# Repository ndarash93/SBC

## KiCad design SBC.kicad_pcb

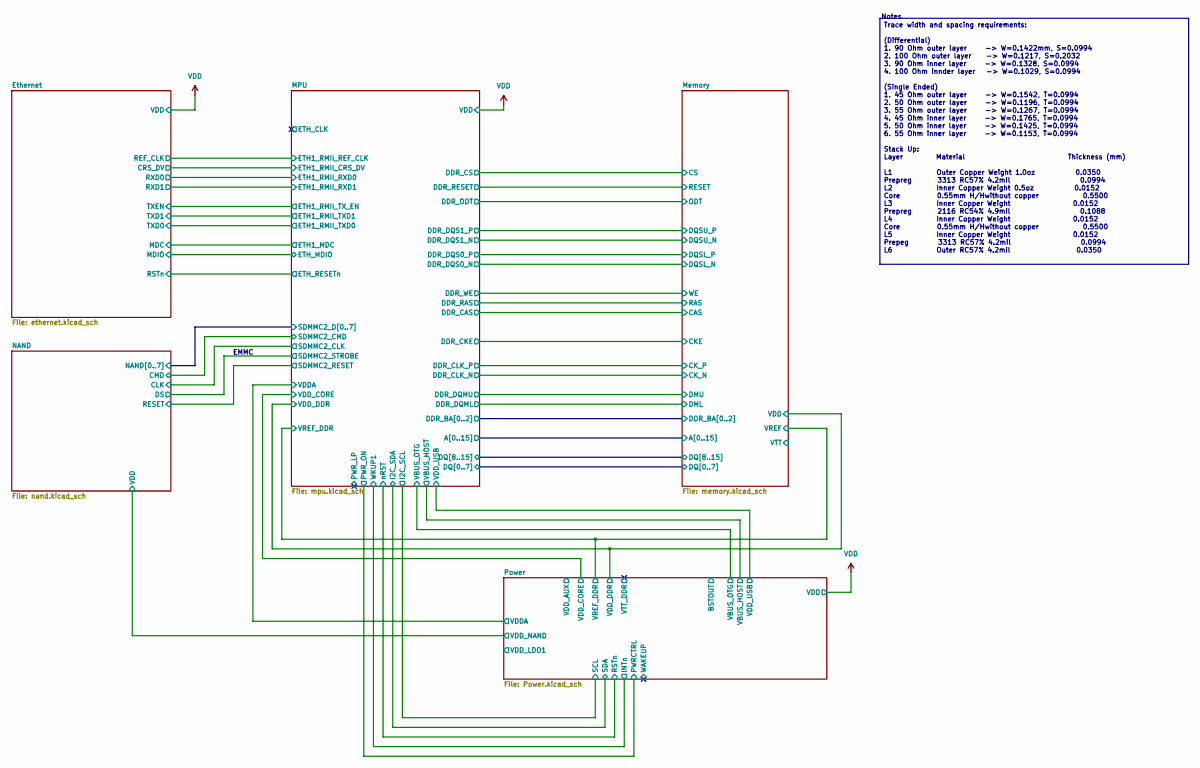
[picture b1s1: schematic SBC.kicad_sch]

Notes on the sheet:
Notes
EMMC
Trace width and spacing requirements: (Differential) 1. 90 Ohm outer layer -> W=0.1422mm, S=0.0994 2. 100 Ohm outer layer -> W=0.1217, S=0.2032 3. 90 Ohm inner layer -> W=0.1328, S=0.0994 4. 100 Ohm innder layer -> W=0.1029, S=0.0994 (Single Ended) 1. 45 Ohm outer layer -> W=0.1542, T=0.0994 2. 50 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

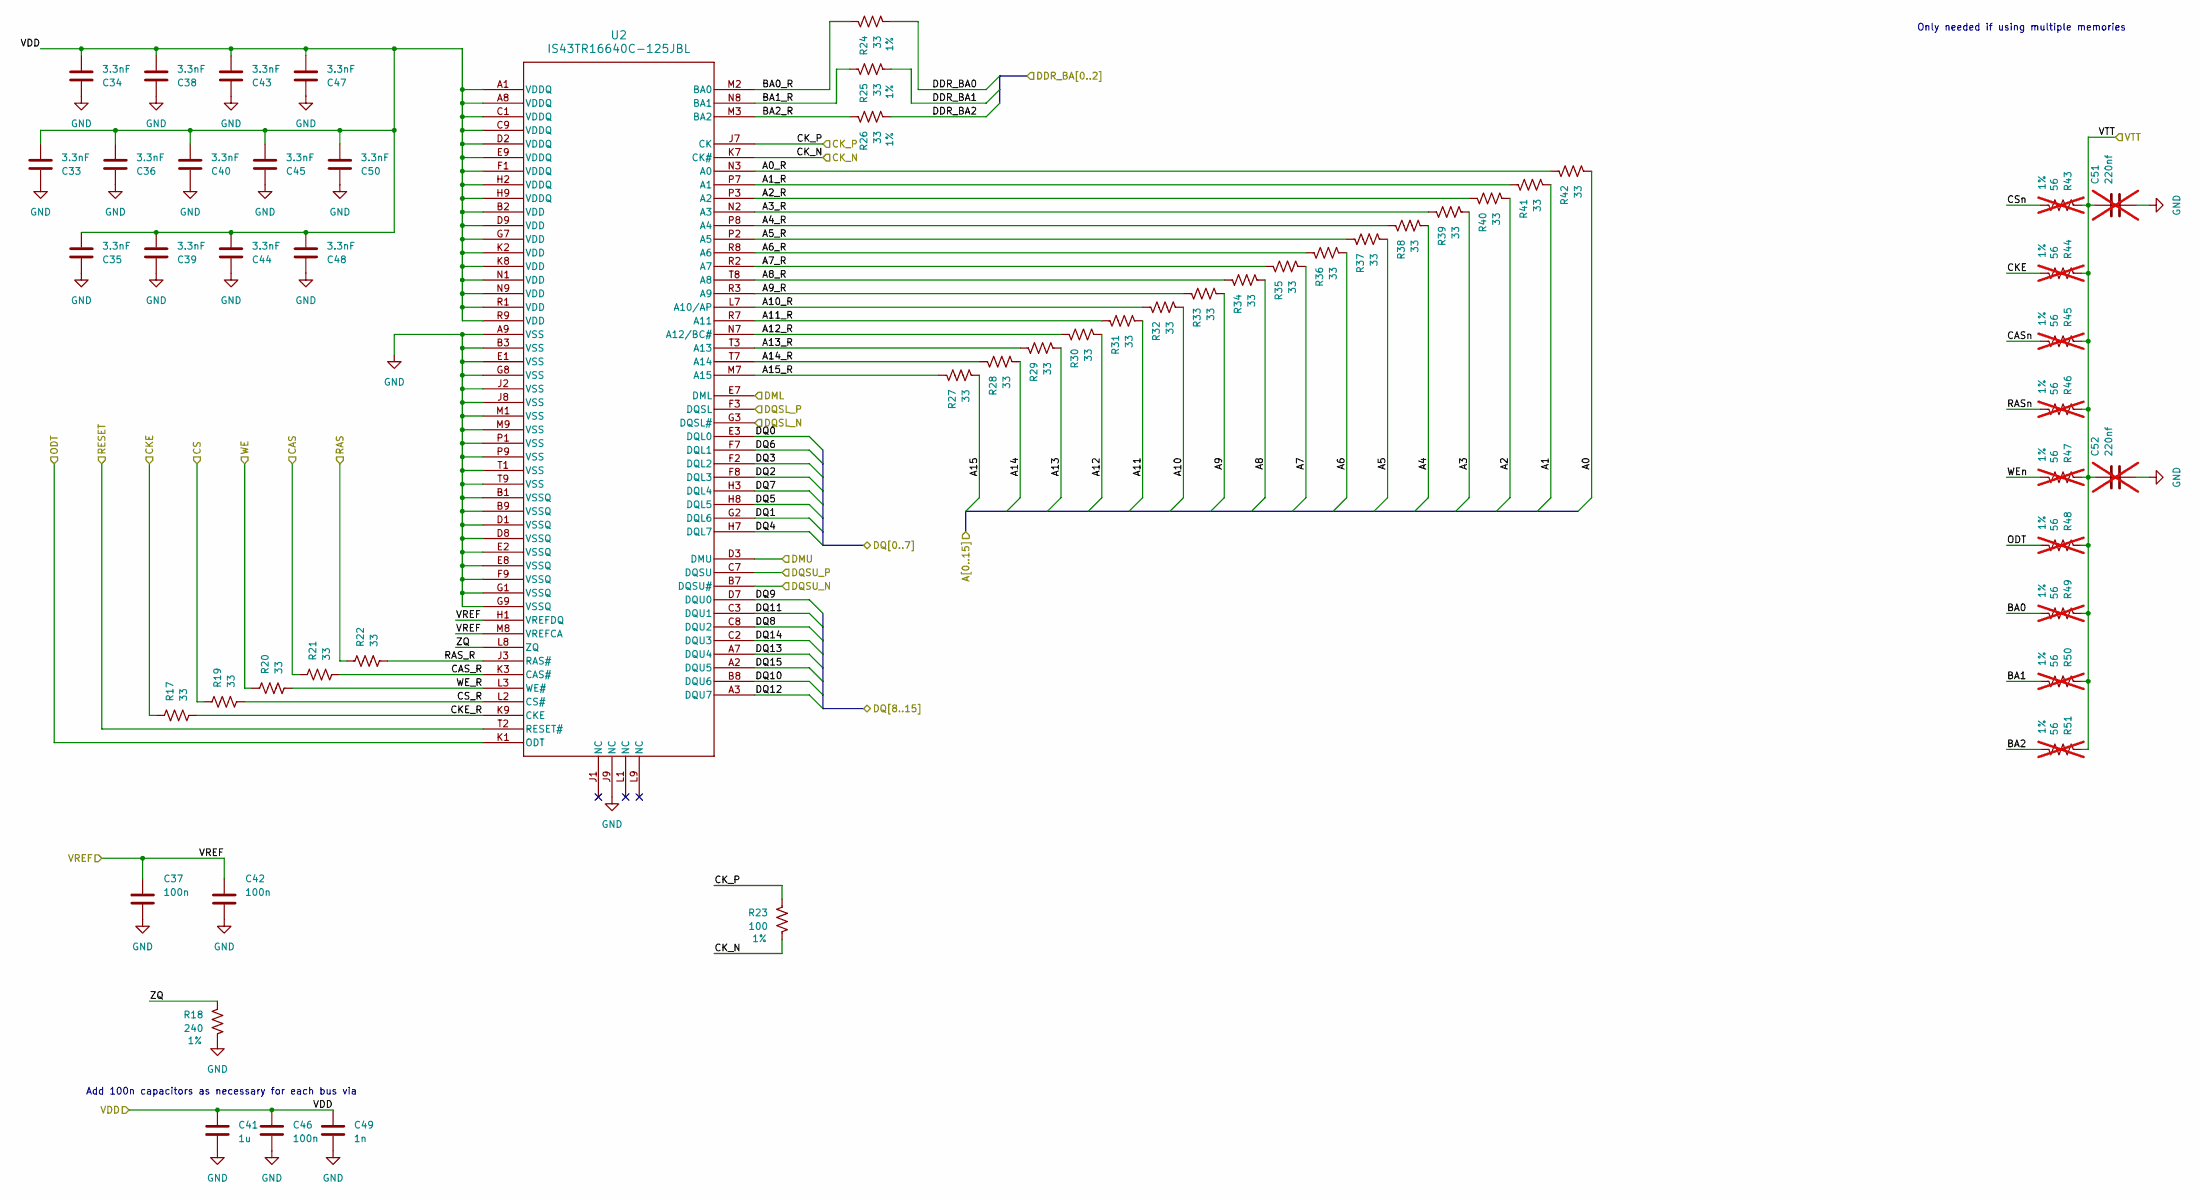
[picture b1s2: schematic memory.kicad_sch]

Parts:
C33, C34, C35, C36, C38, C39, C40, C43, C44, C45, C47, C48, C50: 3.3nF; C_0201_0603Metric
C37, C42: 100n; C_0201_0603Metric
C41: 1u; C_0402_1005Metric
C46: 100n; C_0402_1005Metric
C49: 1n; C_0201_0603Metric
C51, C52: 220nf; TBD; not fitted
R17, R19, R20, R21, R22, R24, R25, R26, R27, R28, R29, R30, R31, R32, R33, R34, R35, R36, R37, R38, R39, R40, R41, R42: 33; R_0402_1005Metric
R18: 240; R_0201_0603Metric
R23: 100; R_0201_0603Metric
R43, R44, R45, R46, R47, R48, R49, R50, R51: 56; not fitted
U2: IS43TR16640C-125JBL; TW-BGA96L_9X13X1.2_ISI

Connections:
/MPU/A0: R42.2; also elsewhere on the board
/MPU/A1: R41.2; also elsewhere on the board
/MPU/A2: R40.2; also elsewhere on the board
/MPU/A3: R39.2; also elsewhere on the board
/MPU/A4: R38.2; also elsewhere on the board
/MPU/A5: R37.2; also elsewhere on the board
/MPU/A6: R36.2; also elsewhere on the board
/MPU/A7: R35.2; also elsewhere on the board
/MPU/A8: R34.2; also elsewhere on the board
/MPU/A9: R33.2; also elsewhere on the board
/MPU/A10: R32.2; also elsewhere on the board
/MPU/A11: R31.2; also elsewhere on the board
/MPU/A12: R30.2; also elsewhere on the board
/MPU/A13: R29.2; also elsewhere on the board
/MPU/A14: R28.2; also elsewhere on the board
/MPU/A15: R27.2; also elsewhere on the board
/MPU/DDR_BA0: R24.2; also elsewhere on the board
/MPU/DDR_BA1: R25.2; also elsewhere on the board
/MPU/DDR_BA2: R26.2; also elsewhere on the board
/MPU/DDR_CAS: R21.1; also elsewhere on the board
/MPU/DDR_CKE: R17.1; also elsewhere on the board
/MPU/DDR_CLKN: R23.2, U2.K7 (CK#); also elsewhere on the board
/MPU/DDR_CLKP: R23.1, U2.J7 (CK); also elsewhere on the board
/MPU/DDR_CS: R19.1; also elsewhere on the board
/MPU/DDR_DQM0: U2.E7 (DML); also elsewhere on the board
/MPU/DDR_DQM1: U2.D3 (DMU); also elsewhere on the board
/MPU/DDR_DQS0_N: U2.G3 (DQSL#); also elsewhere on the board
/MPU/DDR_DQS0_P: U2.F3 (DQSL); also elsewhere on the board
/MPU/DDR_DQS1_N: U2.B7 (DQSU#); also elsewhere on the board
/MPU/DDR_DQS1_P: U2.C7 (DQSU); also elsewhere on the board
/MPU/DDR_RAS: R22.1; also elsewhere on the board
/MPU/DDR_RESETn: U2.T2 (RESET#); also elsewhere on the board
/MPU/DDR_VREF: C37.1, C42.1, U2.H1 (VREFDQ), U2.M8 (VREFCA); also elsewhere on the board
/MPU/DDR_WE: R20.1; also elsewhere on the board
/MPU/DQ0: U2.E3 (DQL0); also elsewhere on the board
/MPU/DQ1: U2.G2 (DQL6); also elsewhere on the board
/MPU/DQ2: U2.F8 (DQL3); also elsewhere on the board
/MPU/DQ3: U2.F2 (DQL2); also elsewhere on the board
/MPU/DQ4: U2.H7 (DQL7); also elsewhere on the board
/MPU/DQ5: U2.H8 (DQL5); also elsewhere on the board
/MPU/DQ6: U2.F7 (DQL1); also elsewhere on the board
/MPU/DQ7: U2.H3 (DQL4); also elsewhere on the board
/MPU/DQ8: U2.C8 (DQU2); also elsewhere on the board
/MPU/DQ9: U2.D7 (DQU0); also elsewhere on the board
/MPU/DQ10: U2.B8 (DQU6); also elsewhere on the board
/MPU/DQ11: U2.C3 (DQU1); also elsewhere on the board
/MPU/DQ12: U2.A3 (DQU7); also elsewhere on the board
/MPU/DQ13: U2.A7 (DQU4); also elsewhere on the board
/MPU/DQ14: U2.C2 (DQU3); also elsewhere on the board
/MPU/DQ15: U2.A2 (DQU5); also elsewhere on the board
/MPU/VDD_DDR: C33.1, C34.1, C35.1, C36.1, C38.1, C39.1, C40.1, C41.1, C43.1, C44.1, C45.1, C46.1, C47.1, C48.1, C49.1, C50.1, U2.A1 (VDDQ), U2.A8 (VDDQ), U2.B2 (VDD), U2.C1 (VDDQ), U2.C9 (VDDQ), U2.D2 (VDDQ), U2.D9 (VDD), U2.E9 (VDDQ), U2.F1 (VDDQ), U2.G7 (VDD), U2.H2 (VDDQ), U2.H9 (VDDQ), U2.K2 (VDD), U2.K8 (VDD), U2.N1 (VDD), U2.N9 (VDD), U2.R1 (VDD), U2.R9 (VDD); also elsewhere on the board
/Memory/A0_R: R42.1, U2.N3 (A0)
/Memory/A1_R: R41.1, U2.P7 (A1)
/Memory/A2_R: R40.1, U2.P3 (A2)
/Memory/A3_R: R39.1, U2.N2 (A3)
/Memory/A4_R: R38.1, U2.P8 (A4)
/Memory/A5_R: R37.1, U2.P2 (A5)
/Memory/A6_R: R36.1, U2.R8 (A6)
/Memory/A7_R: R35.1, U2.R2 (A7)
/Memory/A8_R: R34.1, U2.T8 (A8)
/Memory/A9_R: R33.1, U2.R3 (A9)
/Memory/A10_R: R32.1, U2.L7 (A10/AP)
/Memory/A11_R: R31.1, U2.R7 (A11)
/Memory/A12_R: R30.1, U2.N7 (A12/BC#)
/Memory/A13_R: R29.1, U2.T3 (A13)
/Memory/A14_R: R28.1, U2.T7 (A14)
/Memory/A15_R: R27.1, U2.M7 (A15)
/Memory/BA0_R: R24.1, U2.M2 (BA0)
/Memory/BA1_R: R25.1, U2.N8 (BA1)
/Memory/BA2_R: R26.1, U2.M3 (BA2)
/Memory/CAS_R: R21.2, U2.K3 (CAS#)
/Memory/CKE_R: R17.2, U2.K9 (CKE)
/Memory/CS_R: R19.2, U2.L2 (CS#)
/Memory/ODT: U2.K1 (ODT); also elsewhere on the board
/Memory/RAS_R: R22.2, U2.J3 (RAS#)
/Memory/WE_R: R20.2, U2.L3 (WE#)
/Memory/ZQ: R18.1, U2.L8 (ZQ)
GND: C33.2, C34.2, C35.2, C36.2, C37.2, C38.2, C39.2, C40.2, C41.2, C42.2, C43.2, C44.2, C45.2, C46.2, C47.2, C48.2, C49.2, C50.2, C51.2, C52.2, R18.2, U2.A9 (VSS), U2.B1 (VSSQ), U2.B3 (VSS), U2.B9 (VSSQ), U2.D1 (VSSQ), U2.D8 (VSSQ), U2.E1 (VSS), U2.E2 (VSSQ), U2.E8 (VSSQ), U2.F9 (VSSQ), U2.G1 (VSSQ), U2.G8 (VSS), U2.G9 (VSSQ), U2.J2 (VSS), U2.J8 (VSS), U2.J9 (NC), U2.M1 (VSS), U2.M9 (VSS), U2.P1 (VSS), U2.P9 (VSS), U2.T1 (VSS), U2.T9 (VSS); also elsewhere on the board
unnamed: C51.1, C52.1, R43.1, R44.1, R45.1, R46.1, R47.1, R48.1, R49.1, R50.1, R51.1

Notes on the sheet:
Add 100n capacitors as necessary for each bus via
Only needed if using multiple memories

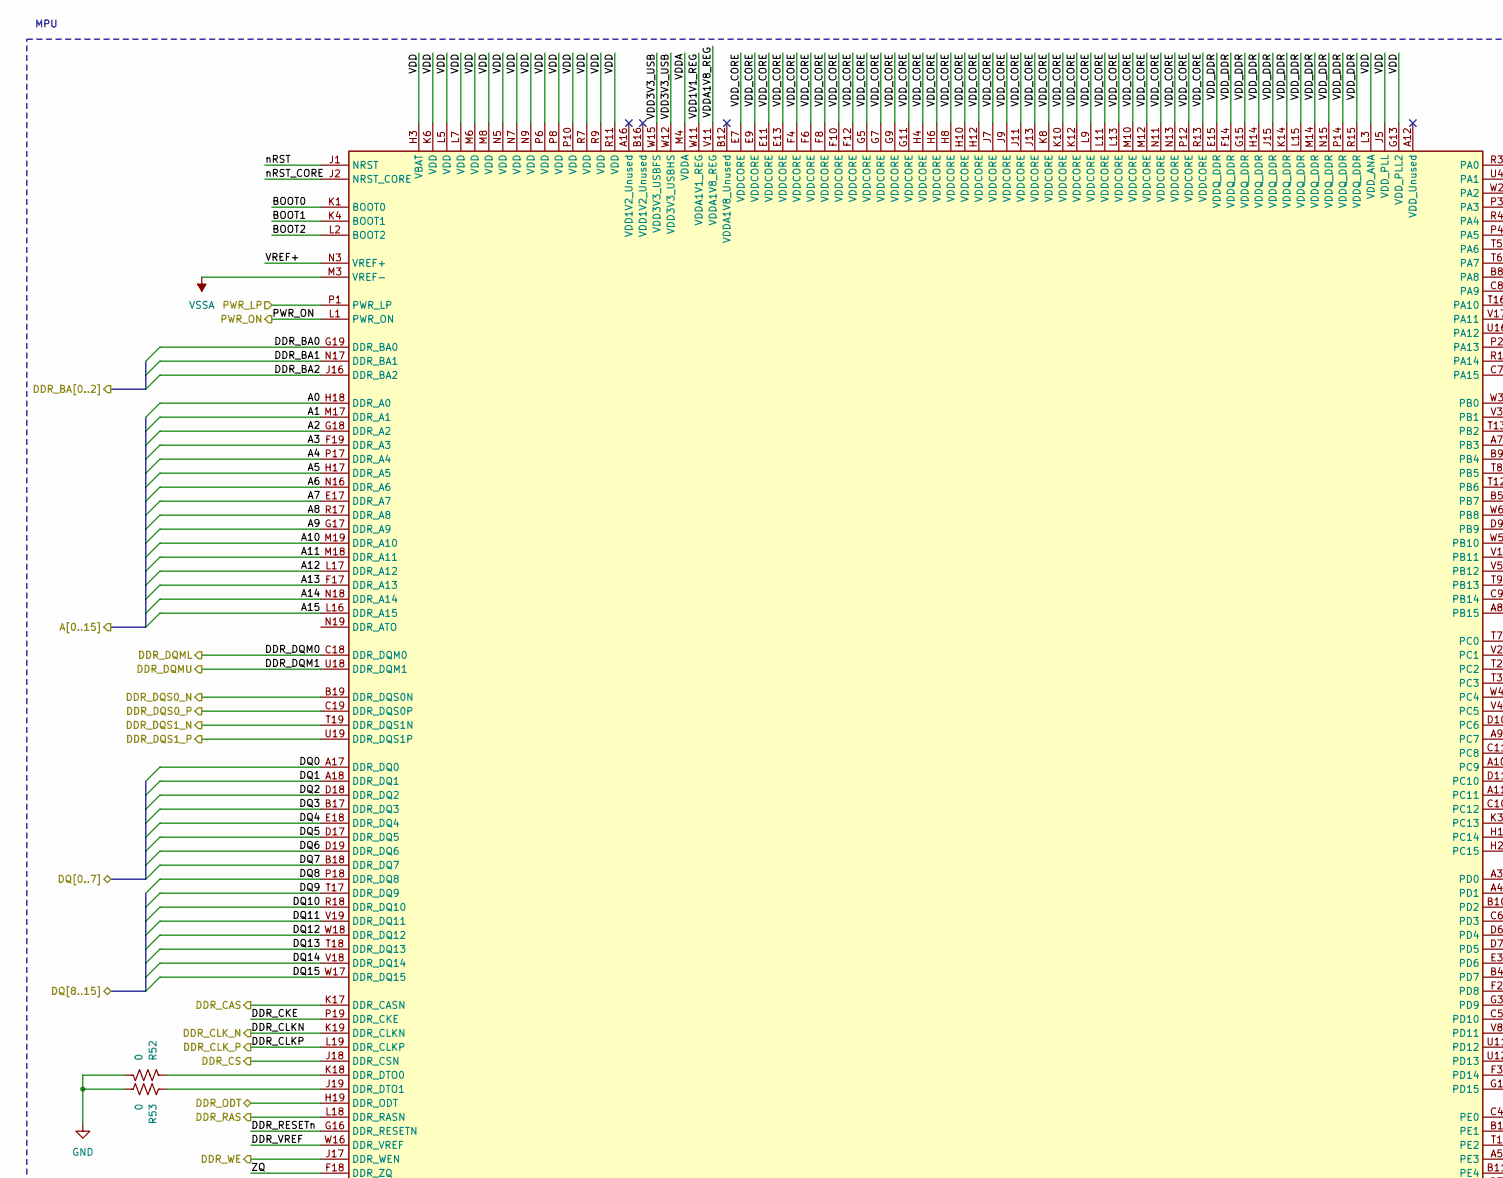
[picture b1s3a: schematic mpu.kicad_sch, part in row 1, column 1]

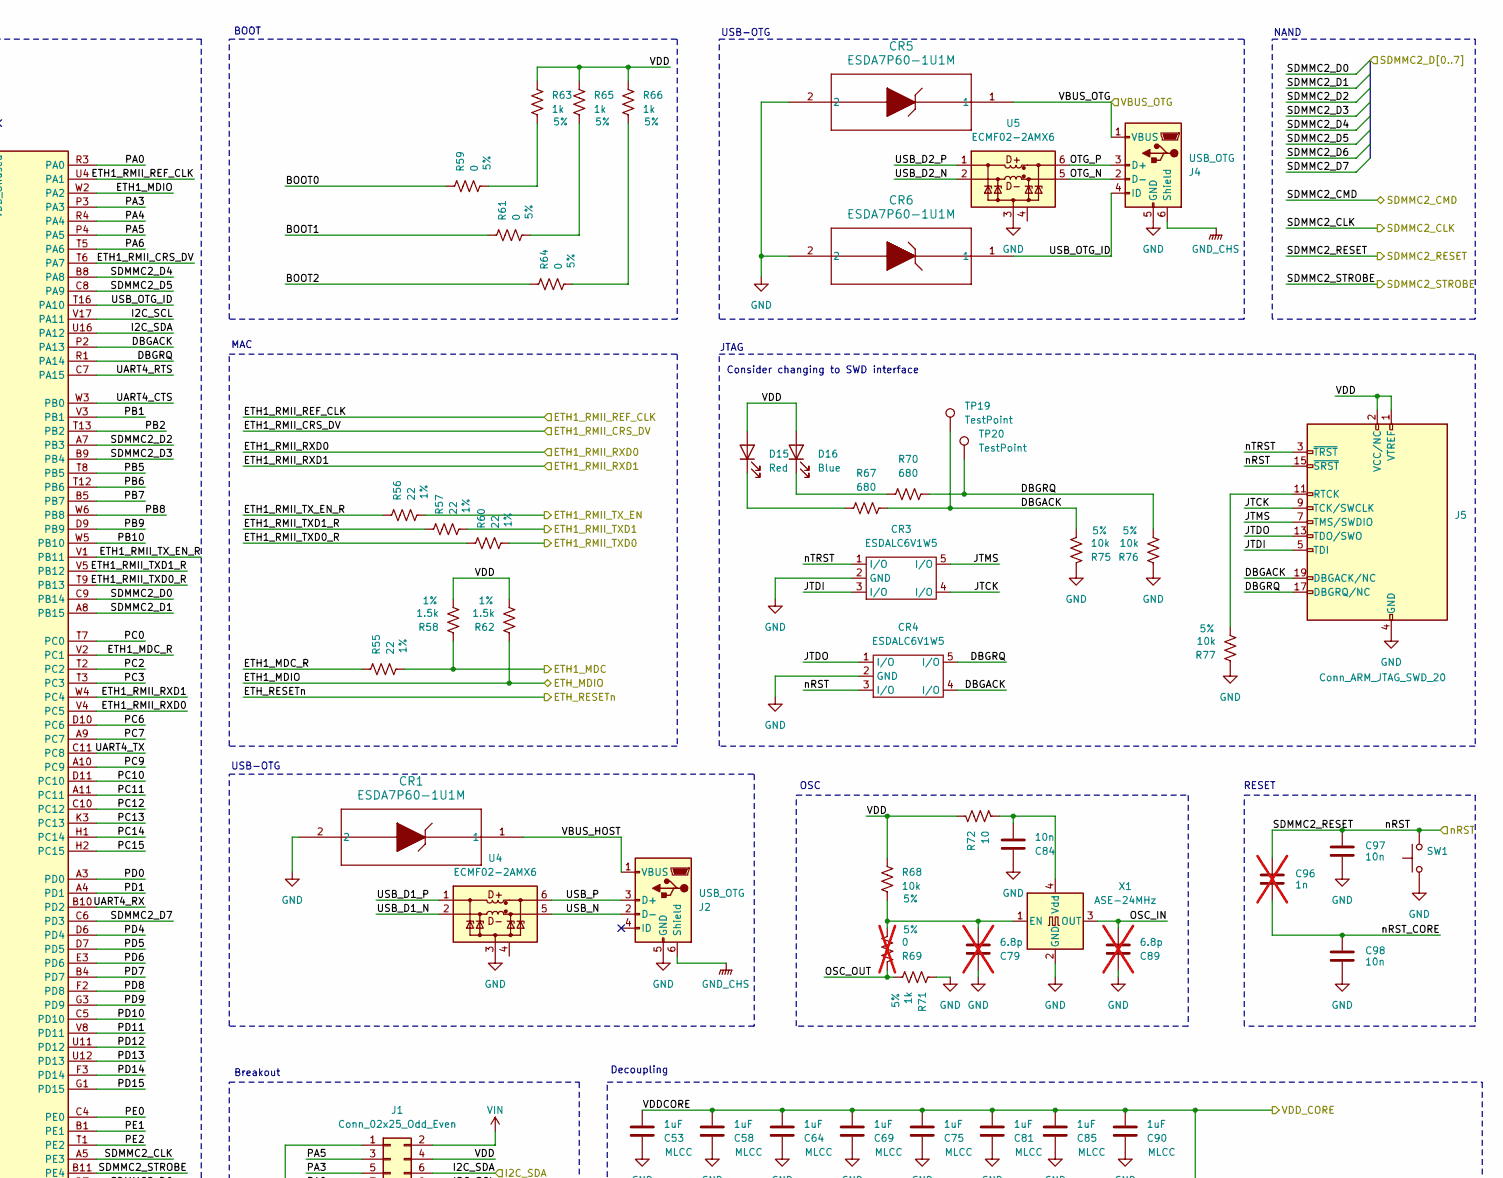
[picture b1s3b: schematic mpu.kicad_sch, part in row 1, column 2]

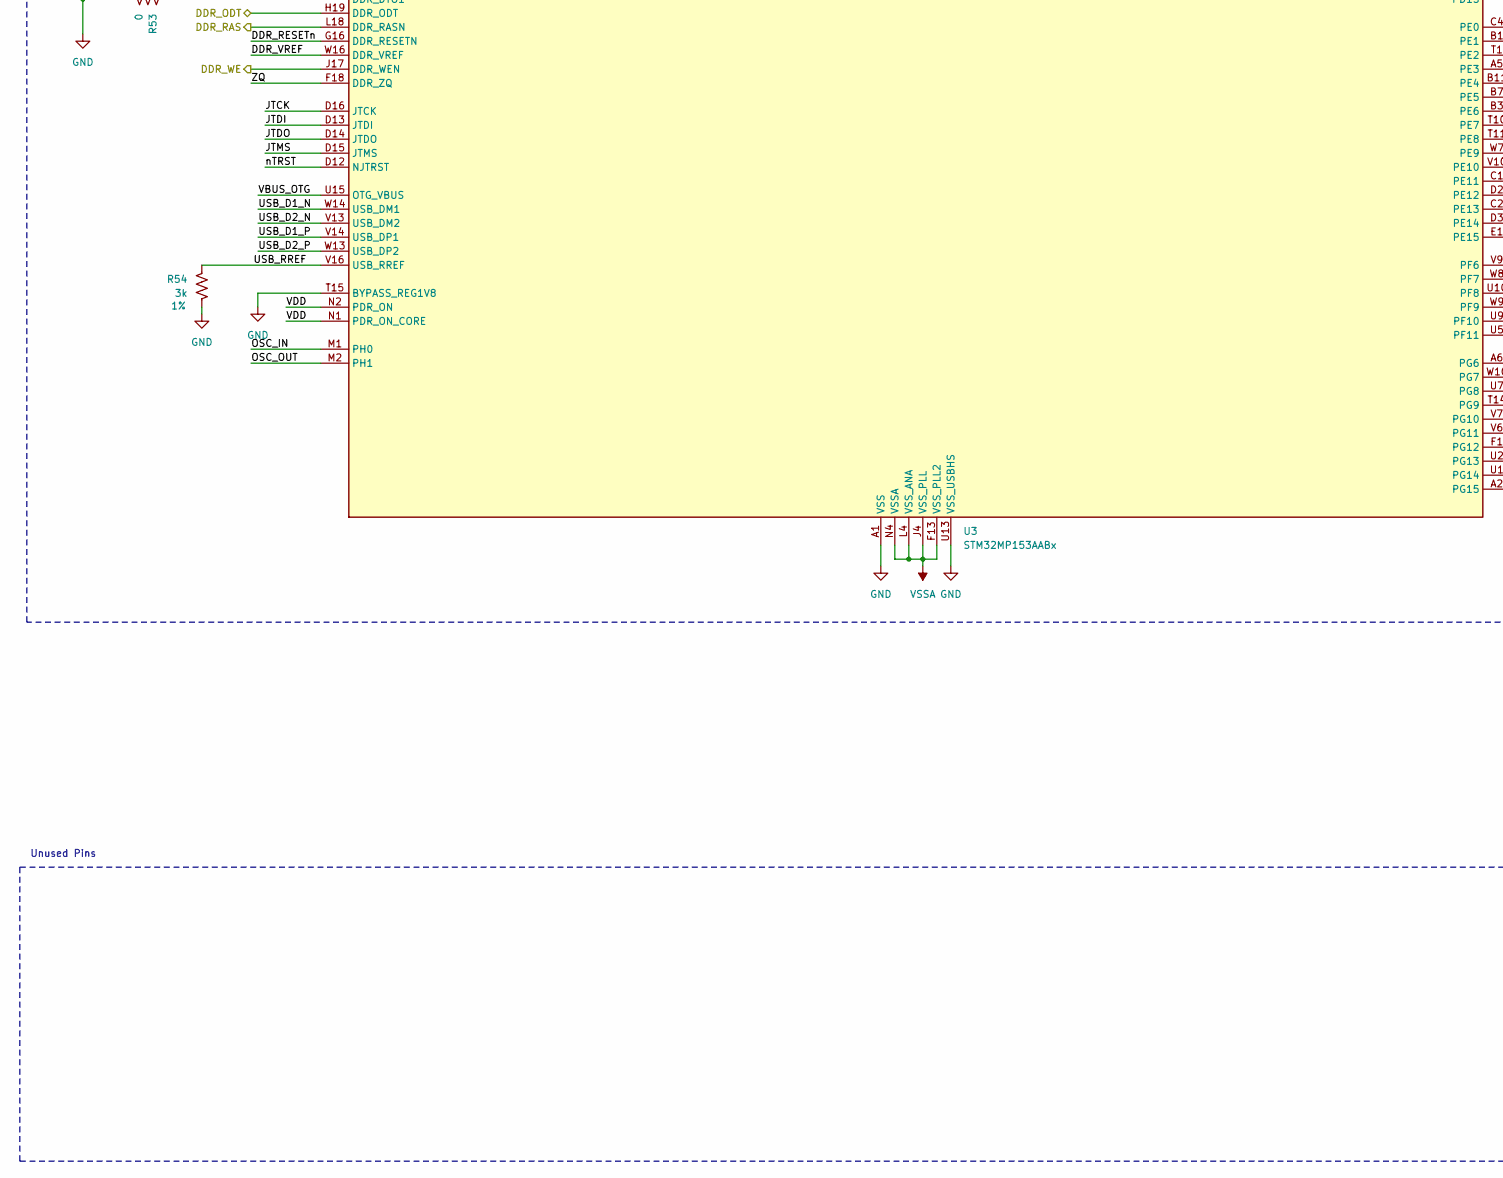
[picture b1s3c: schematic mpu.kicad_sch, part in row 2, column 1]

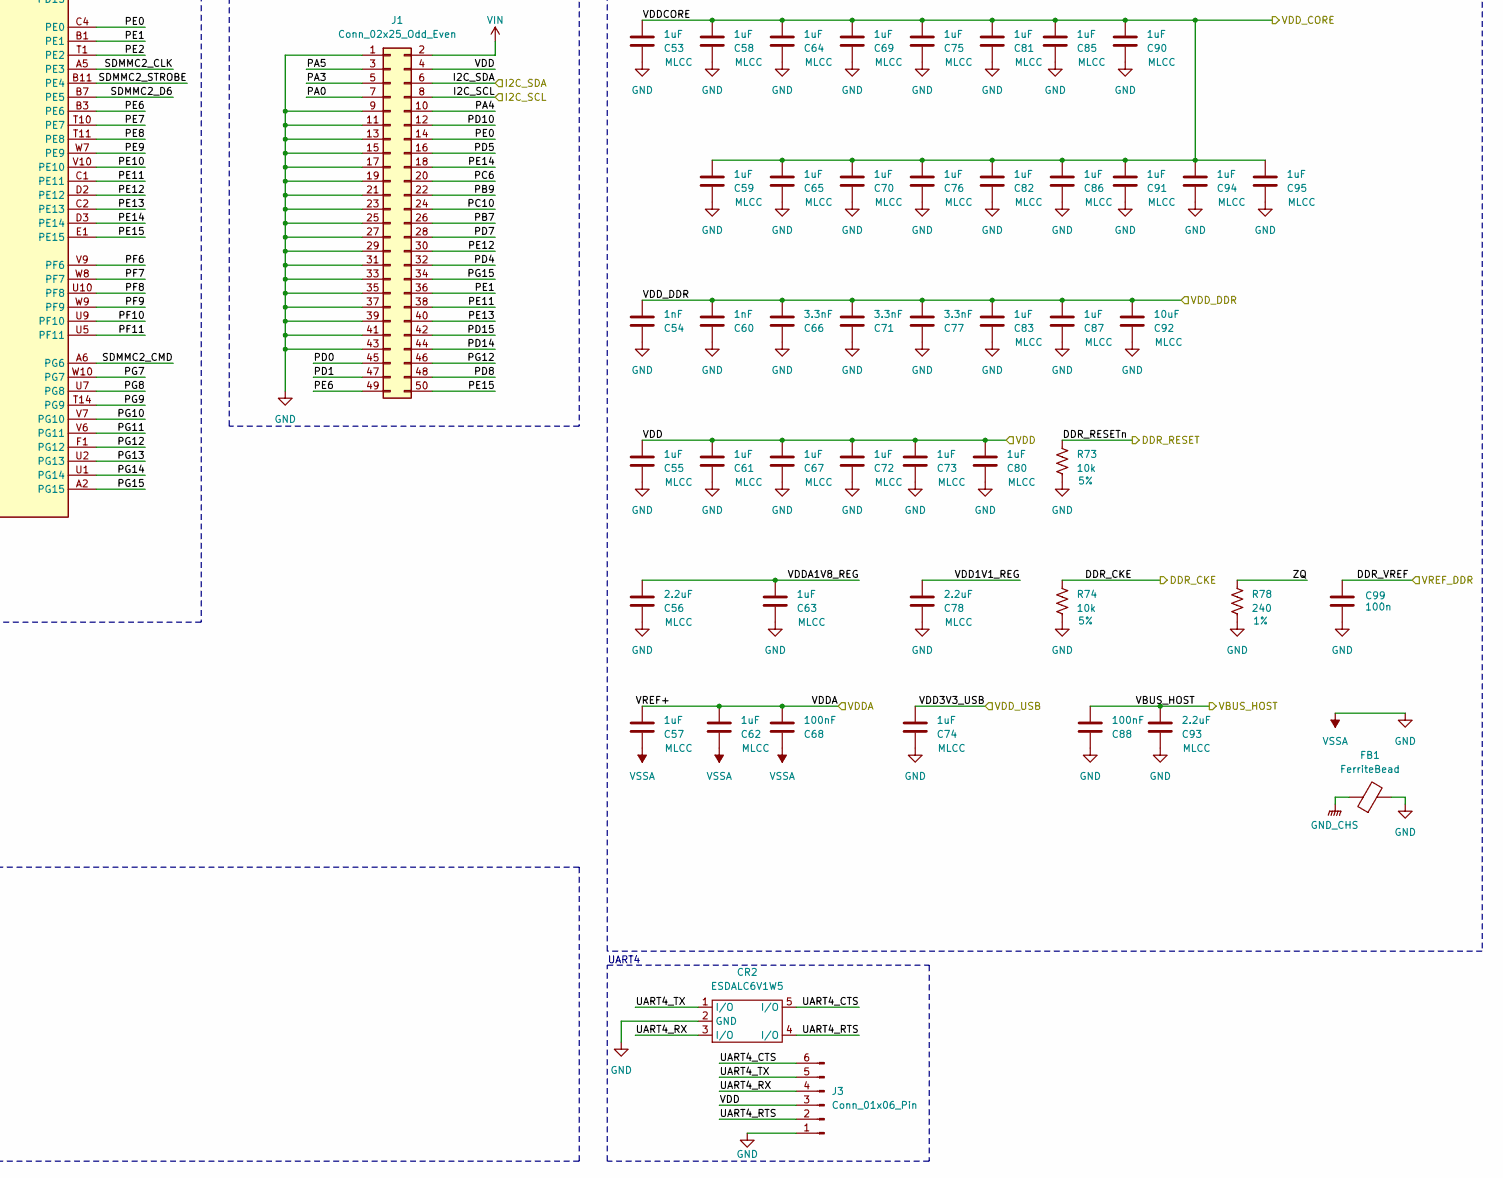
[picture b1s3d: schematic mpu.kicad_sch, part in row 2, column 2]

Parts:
C53, C55, C58, C59, C61, C63, C64, C65, C67, C69, C70, C72, C73, C74, C75, C76, C80, C81, C82, C83, C85, C86, C87, C90, C91, C94, C95: 1uF; C_0201_0603Metric
C54, C60: 1nF; C_0201_0603Metric
C56, C93: 2.2uF; C_0402_1005Metric
C57, C62: 1uF; C_0402_1005Metric
C66, C71, C77: 3.3nF; C_0201_0603Metric
C68: 100nF; C_0201_0603Metric
C78: 2.2uF; C_0201_0603Metric
C79, C89: 6.8p; C_0402_1005Metric; not fitted
C84, C97, C98: 10n; C_0402_1005Metric
C88: 100nF; C_0402_1005Metric
C92: 10uF; C_0402_1005Metric
C96: 1n; C_0402_1005Metric; not fitted
C99: 100n; C_0402_1005Metric
CR1, CR5, CR6: ESDA7P60-1U1M; ZDO_1610_STM
CR2, CR3, CR4: ESDALC6V1W5; SOT323-5L
D15: Red; LED_0603_1608Metric
D16: Blue; LED_0603_1608Metric
FB1: FerriteBead; L_0805_2012Metric; MPN ACML-0805-110-T
J1: Conn_02x25_Odd_Even; PinHeader_2x25_P2.54mm_Vertical
J2, J4: USB_OTG; USB_Micro-B_Amphenol_10103594-0001LF_Horizontal
J3: Conn_01x06_Pin; PinSocket_1x06_P2.54mm_Vertical
J5: Conn_ARM_JTAG_SWD_20; PinHeader_2x10_P1.27mm_Vertical
R52, R53, R59, R61, R64: 0; R_0402_1005Metric
R54: 3k; R_0201_0603Metric
R55, R56, R57, R60: 22; R_0402_1005Metric
R58, R62: 1.5k; R_0402_1005Metric
R63, R65, R66, R71: 1k; R_0402_1005Metric
R67, R70: 680; R_0402_1005Metric
R68, R73, R75, R76, R77: 10k; R_0402_1005Metric
R69: 0; R_0402_1005Metric; not fitted
R72: 10; R_0402_1005Metric
R74: 10k; R_0201_0603Metric
R78: 240; R_0402_1005Metric
SW1: SW_Push_1P1T_NO_CK_KSC6xxJ
TP19, TP20: TestPoint; TestPoint-0.5mm
U3: STM32MP153AABx; ST_LFBGA-354_16x16mm_Layout19x19_P0.8mm
U4, U5: ECMF02-2AMX6; ST_UQFN-6L_1.5x1.7mm_P0.5mm
X1: ASE-24MHz; Oscillator_SMD_Abracon_ASE-4Pin_3.2x2.5mm

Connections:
/Ethernet/MDC: R55.2, R58.1; also elsewhere on the board
/Ethernet/MODE0: U3.V4 (PC5); also elsewhere on the board
/Ethernet/MODE1: U3.W4 (PC4); also elsewhere on the board
/Ethernet/MODE2: U3.T6 (PA7); also elsewhere on the board
/Ethernet/REFCLKO: U3.U4 (PA1); also elsewhere on the board
/Ethernet/TXD0: R60.2; also elsewhere on the board
/Ethernet/TXD1: R57.2; also elsewhere on the board
/Ethernet/TXEN: R56.2; also elsewhere on the board
/MPU/A0: U3.H18 (DDR_A0); also elsewhere on the board
/MPU/A1: U3.M17 (DDR_A1); also elsewhere on the board
/MPU/A2: U3.G18 (DDR_A2); also elsewhere on the board
/MPU/A3: U3.F19 (DDR_A3); also elsewhere on the board
/MPU/A4: U3.P17 (DDR_A4); also elsewhere on the board
/MPU/A5: U3.H17 (DDR_A5); also elsewhere on the board
/MPU/A6: U3.N16 (DDR_A6); also elsewhere on the board
/MPU/A7: U3.E17 (DDR_A7); also elsewhere on the board
/MPU/A8: U3.R17 (DDR_A8); also elsewhere on the board
/MPU/A9: U3.G17 (DDR_A9); also elsewhere on the board
/MPU/A10: U3.M19 (DDR_A10); also elsewhere on the board
/MPU/A11: U3.M18 (DDR_A11); also elsewhere on the board
/MPU/A12: U3.L17 (DDR_A12); also elsewhere on the board
/MPU/A13: U3.F17 (DDR_A13); also elsewhere on the board
/MPU/A14: U3.N18 (DDR_A14); also elsewhere on the board
/MPU/A15: U3.L16 (DDR_A15); also elsewhere on the board
/MPU/BOOT0: R59.1, U3.K1 (BOOT0)
/MPU/BOOT1: R61.1, U3.K4 (BOOT1)
/MPU/BOOT2: R64.1, U3.L2 (BOOT2)
/MPU/DBGACK: CR4.4 (I/O), J5.19 (DBGACK/NC), R67.1, R75.2, TP19.1, U3.P2 (PA13)
/MPU/DBGRQ: CR4.5 (I/O), J5.17 (DBGRQ/NC), R70.1, R76.2, TP20.1, U3.R1 (PA14)
/MPU/DDR_BA0: U3.G19 (DDR_BA0); also elsewhere on the board
/MPU/DDR_BA1: U3.N17 (DDR_BA1); also elsewhere on the board
/MPU/DDR_BA2: U3.J16 (DDR_BA2); also elsewhere on the board
/MPU/DDR_CAS: U3.K17 (DDR_CASN); also elsewhere on the board
/MPU/DDR_CKE: R74.1, U3.P19 (DDR_CKE); also elsewhere on the board
/MPU/DDR_CLKN: U3.K19 (DDR_CLKN); also elsewhere on the board
/MPU/DDR_CLKP: U3.L19 (DDR_CLKP); also elsewhere on the board
/MPU/DDR_CS: U3.J18 (DDR_CSN); also elsewhere on the board
/MPU/DDR_DQM0: U3.C18 (DDR_DQM0); also elsewhere on the board
/MPU/DDR_DQM1: U3.U18 (DDR_DQM1); also elsewhere on the board
/MPU/DDR_DQS0_N: U3.B19 (DDR_DQS0N); also elsewhere on the board
/MPU/DDR_DQS0_P: U3.C19 (DDR_DQS0P); also elsewhere on the board
/MPU/DDR_DQS1_N: U3.T19 (DDR_DQS1N); also elsewhere on the board
/MPU/DDR_DQS1_P: U3.U19 (DDR_DQS1P); also elsewhere on the board
/MPU/DDR_RAS: U3.L18 (DDR_RASN); also elsewhere on the board
/MPU/DDR_RESETn: R73.1, U3.G16 (DDR_RESETN); also elsewhere on the board
/MPU/DDR_VREF: C99.1, U3.W16 (DDR_VREF); also elsewhere on the board
/MPU/DDR_WE: U3.J17 (DDR_WEN); also elsewhere on the board
/MPU/DQ0: U3.A17 (DDR_DQ0); also elsewhere on the board
/MPU/DQ1: U3.A18 (DDR_DQ1); also elsewhere on the board
/MPU/DQ2: U3.D18 (DDR_DQ2); also elsewhere on the board
/MPU/DQ3: U3.B17 (DDR_DQ3); also elsewhere on the board
/MPU/DQ4: U3.E18 (DDR_DQ4); also elsewhere on the board
/MPU/DQ5: U3.D17 (DDR_DQ5); also elsewhere on the board
/MPU/DQ6: U3.D19 (DDR_DQ6); also elsewhere on the board
/MPU/DQ7: U3.B18 (DDR_DQ7); also elsewhere on the board
/MPU/DQ8: U3.P18 (DDR_DQ8); also elsewhere on the board
/MPU/DQ9: U3.T17 (DDR_DQ9); also elsewhere on the board
/MPU/DQ10: U3.R18 (DDR_DQ10); also elsewhere on the board
/MPU/DQ11: U3.V19 (DDR_DQ11); also elsewhere on the board
/MPU/DQ12: U3.W18 (DDR_DQ12); also elsewhere on the board
/MPU/DQ13: U3.T18 (DDR_DQ13); also elsewhere on the board
/MPU/DQ14: U3.V18 (DDR_DQ14); also elsewhere on the board
/MPU/DQ15: U3.W17 (DDR_DQ15); also elsewhere on the board
/MPU/ETH1_MDC_R: R55.1, U3.V2 (PC1)
/MPU/ETH1_MDIO: R62.1, U3.W2 (PA2); also elsewhere on the board
/MPU/ETH1_RMII_TXD0_R: R60.1, U3.T9 (PB13)
/MPU/ETH1_RMII_TXD1_R: R57.1, U3.V5 (PB12)
/MPU/ETH1_RMII_TX_EN_R: R56.1, U3.V1 (PB11)
/MPU/I2C_SCL: J1.8, U3.V17 (PA11); also elsewhere on the board
/MPU/I2C_SDA: J1.6, U3.U16 (PA12); also elsewhere on the board
/MPU/JTCK: CR3.4 (I/O), J5.9 (TCK/SWCLK), U3.D16 (JTCK)
/MPU/JTDI: CR3.3 (I/O), J5.5 (TDI), U3.D13 (JTDI)
/MPU/JTDO: CR4.1 (I/O), J5.13 (TDO/SWO), U3.D14 (JTDO)
/MPU/JTMS: CR3.5 (I/O), J5.7 (TMS/SWDIO), U3.D15 (JTMS)
/MPU/OSC_IN: C89.1, U3.M1 (PH0), X1.3 (OUT)
/MPU/OSC_OUT: R69.1, R71.2, U3.M2 (PH1)
/MPU/OTG_N: J4.2 (D-), U5.5 (D-_out)
/MPU/OTG_P: J4.3 (D+), U5.6 (D+_out)
/MPU/PA0: J1.7, U3.R3 (PA0)
/MPU/PA3: J1.5, U3.P3 (PA3)
/MPU/PA4: J1.10, U3.R4 (PA4)
/MPU/PA5: J1.3, U3.P4 (PA5)
/MPU/PA6: U3.T5 (PA6)
/MPU/PB1: U3.V3 (PB1)
/MPU/PB2: U3.T13 (PB2)
/MPU/PB5: U3.T8 (PB5)
/MPU/PB6: U3.T12 (PB6)
/MPU/PB7: J1.26, U3.B5 (PB7)
/MPU/PB8: U3.W6 (PB8)
/MPU/PB9: J1.22, U3.D9 (PB9)
/MPU/PB10: U3.W5 (PB10)
/MPU/PC0: U3.T7 (PC0)
/MPU/PC2: U3.T2 (PC2)
/MPU/PC3: U3.T3 (PC3)
/MPU/PC6: J1.20, U3.D10 (PC6)
/MPU/PC7: U3.A9 (PC7)
/MPU/PC9: U3.A10 (PC9)
/MPU/PC10: J1.24, U3.D11 (PC10)
/MPU/PC11: U3.A11 (PC11)
/MPU/PC12: U3.C10 (PC12)
/MPU/PC13: U3.K3 (PC13)
/MPU/PC14: U3.H1 (PC14)
/MPU/PC15: U3.H2 (PC15)
/MPU/PD0: J1.45, U3.A3 (PD0)
/MPU/PD1: J1.47, U3.A4 (PD1)
/MPU/PD4: J1.32, U3.D6 (PD4)
/MPU/PD5: J1.16, U3.D7 (PD5)
/MPU/PD6: U3.E3 (PD6)
/MPU/PD7: J1.28, U3.B4 (PD7)
/MPU/PD8: J1.48, U3.F2 (PD8)
/MPU/PD9: U3.G3 (PD9)
/MPU/PD10: J1.12, U3.C5 (PD10)
/MPU/PD11: U3.V8 (PD11)
/MPU/PD12: U3.U11 (PD12)
/MPU/PD13: U3.U12 (PD13)
/MPU/PD14: J1.44, U3.F3 (PD14)
/MPU/PD15: J1.42, U3.G1 (PD15)
/MPU/PE0: J1.14, U3.C4 (PE0)
/MPU/PE1: J1.36, U3.B1 (PE1)
/MPU/PE2: U3.T1 (PE2)
/MPU/PE6: J1.49, U3.B3 (PE6)
/MPU/PE7: U3.T10 (PE7)
/MPU/PE8: U3.T11 (PE8)
/MPU/PE9: U3.W7 (PE9)
/MPU/PE10: U3.V10 (PE10)
/MPU/PE11: J1.38, U3.C1 (PE11)
/MPU/PE12: J1.30, U3.D2 (PE12)
/MPU/PE13: J1.40, U3.C2 (PE13)
/MPU/PE14: J1.18, U3.D3 (PE14)
/MPU/PE15: J1.50, U3.E1 (PE15)
/MPU/PF6: U3.V9 (PF6)
/MPU/PF7: U3.W8 (PF7)
/MPU/PF8: U3.U10 (PF8)
/MPU/PF9: U3.W9 (PF9)
/MPU/PF10: U3.U9 (PF10)
/MPU/PF11: U3.U5 (PF11)
/MPU/PG7: U3.W10 (PG7)
/MPU/PG8: U3.U7 (PG8)
/MPU/PG9: U3.T14 (PG9)
/MPU/PG10: U3.V7 (PG10)
/MPU/PG11: U3.V6 (PG11)
/MPU/PG12: J1.46, U3.F1 (PG12)
/MPU/PG13: U3.U2 (PG13)
/MPU/PG14: U3.U1 (PG14)
/MPU/PG15: J1.34, U3.A2 (PG15)
/MPU/PWR_LP: U3.P1 (PWR_LP)
/MPU/PWR_ON: U3.L1 (PWR_ON); also elsewhere on the board
/MPU/SDMMC2_CLK: U3.A5 (PE3); also elsewhere on the board
/MPU/SDMMC2_CMD: U3.A6 (PG6); also elsewhere on the board
/MPU/SDMMC2_D0: U3.C9 (PB14); also elsewhere on the board
/MPU/SDMMC2_D1: U3.A8 (PB15); also elsewhere on the board
/MPU/SDMMC2_D2: U3.A7 (PB3); also elsewhere on the board
/MPU/SDMMC2_D3: U3.B9 (PB4); also elsewhere on the board
/MPU/SDMMC2_D4: U3.B8 (PA8); also elsewhere on the board
/MPU/SDMMC2_D5: U3.C8 (PA9); also elsewhere on the board
/MPU/SDMMC2_D6: U3.B7 (PE5); also elsewhere on the board
/MPU/SDMMC2_D7: U3.C6 (PD3); also elsewhere on the board
/MPU/SDMMC2_RESET: C96.1, C97.1, CR4.3 (I/O), J5.15 (~SRST), SW1.2, U3.J1 (NRST); also elsewhere on the board
/MPU/SDMMC2_STROBE: U3.B11 (PE4); also elsewhere on the board
/MPU/UART4_CTS: CR2.5 (I/O), J3.6, U3.W3 (PB0)
/MPU/UART4_RTS: CR2.4 (I/O), J3.2, U3.C7 (PA15)
/MPU/UART4_RX: CR2.3 (I/O), J3.4, U3.B10 (PD2)
/MPU/UART4_TX: CR2.1 (I/O), J3.5, U3.C11 (PC8)
/MPU/USB_D1_N: U3.W14 (USB_DM1), U4.2 (D-_in)
/MPU/USB_D1_P: U3.V14 (USB_DP1), U4.1 (D+_in)
/MPU/USB_D2_N: U3.V13 (USB_DM2), U5.2 (D-_in)
/MPU/USB_D2_P: U3.W13 (USB_DP2), U5.1 (D+_in)
/MPU/USB_N: J2.2 (D-), U4.5 (D-_out)
/MPU/USB_OTG_ID: CR6.1, J4.4 (ID), U3.T16 (PA10)
/MPU/USB_P: J2.3 (D+), U4.6 (D+_out)
/MPU/USB_RREF: R54.1, U3.V16 (USB_RREF)
/MPU/VBUS_HOST: C88.1, C93.1, CR1.1, J2.1 (VBUS); also elsewhere on the board
/MPU/VBUS_OTG: CR5.1, J4.1 (VBUS), U3.U15 (OTG_VBUS); also elsewhere on the board
/MPU/VDD1V1_REG: C78.1, U3.W11 (VDDA1V1_REG)
/MPU/VDD3V3_USB: C74.1, U3.W12 (VDD3V3_USBHS), U3.W15 (VDD3V3_USBFS); also elsewhere on the board
/MPU/VDDA: C57.1, C62.1, C68.1, U3.M4 (VDDA), U3.N3 (VREF+); also elsewhere on the board
/MPU/VDDA1V8_REG: C56.1, C63.1, U3.V11 (VDDA1V8_REG)
/MPU/VDDCORE: C53.1, C58.1, C59.1, C64.1, C65.1, C69.1, C70.1, C75.1, C76.1, C81.1, C82.1, C85.1, C86.1, C90.1, C91.1, C94.1, C95.1, U3.E7 (VDDCORE), U3.E9 (VDDCORE), U3.E11 (VDDCORE), U3.E13 (VDDCORE), U3.F4 (VDDCORE), U3.F6 (VDDCORE), U3.F8 (VDDCORE), U3.F10 (VDDCORE), U3.F12 (VDDCORE), U3.G5 (VDDCORE), U3.G7 (VDDCORE), U3.G9 (VDDCORE), U3.G11 (VDDCORE), U3.H4 (VDDCORE), U3.H6 (VDDCORE), U3.H8 (VDDCORE), U3.H10 (VDDCORE), U3.H12 (VDDCORE), U3.J7 (VDDCORE), U3.J9 (VDDCORE), U3.J11 (VDDCORE), U3.J13 (VDDCORE), U3.K8 (VDDCORE), U3.K10 (VDDCORE), U3.K12 (VDDCORE), U3.L9 (VDDCORE), U3.L11 (VDDCORE), U3.L13 (VDDCORE), U3.M10 (VDDCORE), U3.M12 (VDDCORE), U3.N11 (VDDCORE), U3.N13 (VDDCORE), U3.P12 (VDDCORE), U3.R13 (VDDCORE); also elsewhere on the board
/MPU/VDD_DDR: C54.1, C60.1, C66.1, C71.1, C77.1, C83.1, C87.1, C92.1, U3.E15 (VDDQ_DDR), U3.F14 (VDDQ_DDR), U3.G15 (VDDQ_DDR), U3.H14 (VDDQ_DDR), U3.J15 (VDDQ_DDR), U3.K14 (VDDQ_DDR), U3.L15 (VDDQ_DDR), U3.M14 (VDDQ_DDR), U3.N15 (VDDQ_DDR), U3.P14 (VDDQ_DDR), U3.R15 (VDDQ_DDR); also elsewhere on the board
/MPU/ZQ: R78.1, U3.F18 (DDR_ZQ)
/MPU/nRST_CORE: C96.2, C98.1, U3.J2 (NRST_CORE)
/MPU/nTRST: CR3.1 (I/O), J5.3 (~TRST), U3.D12 (NJTRST)
/Memory/ODT: U3.H19 (DDR_ODT); also elsewhere on the board
GND: C53.2, C54.2, C55.2, C56.2, C57.2, C58.2, C59.2, C60.2, C61.2, C62.2, C63.2, C64.2, C65.2, C66.2, C67.2, C68.2, C69.2, C70.2, C71.2, C72.2, C73.2, C74.2, C75.2, C76.2, C77.2, C78.2, C79.2, C80.2, C81.2, C82.2, C83.2, C84.2, C85.2, C86.2, C87.2, C88.2, C89.2, C90.2, C91.2, C92.2, C93.2, C94.2, C95.2, C97.2, C98.2, C99.2, CR1.2, CR2.2 (GND), CR3.2 (GND), CR4.2 (GND), CR5.2, CR6.2, FB1.2, J1.1, J1.9, J1.11, J1.13, J1.15, J1.17, J1.19, J1.21, J1.23, J1.25, J1.27, J1.29, J1.31, J1.33, J1.35, J1.37, J1.39, J1.41, J1.43, J2.5 (GND), J3.1, J4.5 (GND), J5.4 (GND), J5.6 (GND), J5.8 (GND), J5.10 (GND), J5.12 (GND), J5.14 (GND), J5.16 (GND), J5.18 (GND), J5.20 (GND), R52.2, R53.2, R54.2, R71.1, R73.2, R74.2, R75.1, R76.1, R77.1, R78.2, SW1.1, U3.A1 (VSS), U3.A19 (VSS), U3.B2 (VSS), U3.B6 (VSS), U3.C3 (VSS), U3.C12 (VSS), U3.C13 (VSS), U3.C14 (VSS), U3.C15 (VSS), U3.C16 (VSS), U3.C17 (VSS), U3.D1 (VSS), U3.D4 (VSS), U3.D5 (VSS), U3.D8 (VSS), U3.E2 (VSS), U3.E4 (VSS), U3.E5 (VSS), U3.E6 (VSS), U3.E8 (VSS), U3.E10 (VSS), U3.E12 (VSS), U3.E14 (VSS), U3.E16 (VSS), U3.F5 (VSS), U3.F7 (VSS), U3.F9 (VSS), U3.F11 (VSS), U3.F13 (VSS_PLL2), U3.F15 (VSS), U3.G2 (VSS), U3.G4 (VSS), U3.G6 (VSS), U3.G8 (VSS), U3.G10 (VSS), U3.G12 (VSS), U3.G14 (VSS), U3.H5 (VSS), U3.H7 (VSS), U3.H9 (VSS), U3.H11 (VSS), U3.H13 (VSS), U3.H15 (VSS), U3.J3 (VSS), U3.J4 (VSS_PLL), U3.J6 (VSS), U3.J8 (VSS), U3.J10 (VSS), U3.J12 (VSS), U3.J14 (VSS), U3.K2 (VSS), U3.K5 (VSS), U3.K7 (VSS), U3.K9 (VSS), U3.K11 (VSS), U3.K13 (VSS), U3.K15 (VSS), U3.L4 (VSS_ANA), U3.L6 (VSS), U3.L8 (VSS), U3.L10 (VSS), U3.L12 (VSS), U3.L14 (VSS), U3.M3 (VREF-), U3.M5 (VSS), U3.M7 (VSS), U3.M9 (VSS), U3.M11 (VSS), U3.M13 (VSS), U3.M15 (VSS), U3.N4 (VSSA), U3.N6 (VSS), U3.N8 (VSS), U3.N10 (VSS), U3.N12 (VSS), U3.N14 (VSS), U3.P5 (VSSA), U3.P7 (VSS), U3.P9 (VSS), U3.P11 (VSS), U3.P13 (VSS), U3.P15 (VSS), U3.R2 (VSS), U3.R5 (VSSA), U3.R6 (VSS), U3.R8 (VSS), U3.R10 (VSS), U3.R12 (VSS), U3.R14 (VSS), U3.R16 (VSS), U3.T4 (VSS), U3.T15 (BYPASS_REG1V8), U3.U3 (VSS), U3.U6 (VSS), U3.U8 (VSS), U3.U13 (VSS_USBHS), U3.U14 (VSS_USBHS), U3.U17 (VSS), U3.V12 (VSS_USBHS), U3.V15 (VSS_USBHS), U3.W1 (VSS), U3.W19 (VSS), U4.3 (GND), U5.3 (GND), X1.2 (GND); also elsewhere on the board
GND_CHS: FB1.1, J2.6 (Shield), J4.6 (Shield); also elsewhere on the board
unnamed: D15.1 (K), R67.2
unnamed: D16.1 (K), R70.2
unnamed: J5.11 (RTCK), R77.2
unnamed: R59.2, R63.2
unnamed: R61.2, R65.2
unnamed: R64.2, R66.2
unnamed: R52.1, U3.K18 (DDR_DTO0)
unnamed: R53.1, U3.J19 (DDR_DTO1)
unnamed: C79.1, R68.2, R69.2, X1.1 (EN)
unnamed: C84.1, R72.2, X1.4 (Vdd)
VDD: C55.1, C61.1, C67.1, C72.1, C73.1, C80.1, D15.2 (A), D16.2 (A), J1.4, J3.3, J5.1 (VTREF), J5.2 (VCC/NC), R58.2, R62.2, R63.1, R65.1, R66.1, R68.1, R72.1, U3.G13 (VDD_PLL2), U3.H3 (VBAT), U3.J5 (VDD_PLL), U3.K6 (VDD), U3.L3 (VDD_ANA), U3.L5 (VDD), U3.L7 (VDD), U3.M6 (VDD), U3.M8 (VDD), U3.N1 (PDR_ON_CORE), U3.N2 (PDR_ON), U3.N5 (VDD), U3.N7 (VDD), U3.N9 (VDD), U3.P6 (VDD), U3.P8 (VDD), U3.P10 (VDD), U3.R7 (VDD), U3.R9 (VDD), U3.R11 (VDD); also elsewhere on the board
VIN: J1.2; also elsewhere on the board

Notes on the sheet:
Unused Pins
Consider changing to SWD interface
OSC
Breakout
JTAG
RESET
MAC
NAND
USB-OTG
BOOT
UART4
Decoupling
MPU
